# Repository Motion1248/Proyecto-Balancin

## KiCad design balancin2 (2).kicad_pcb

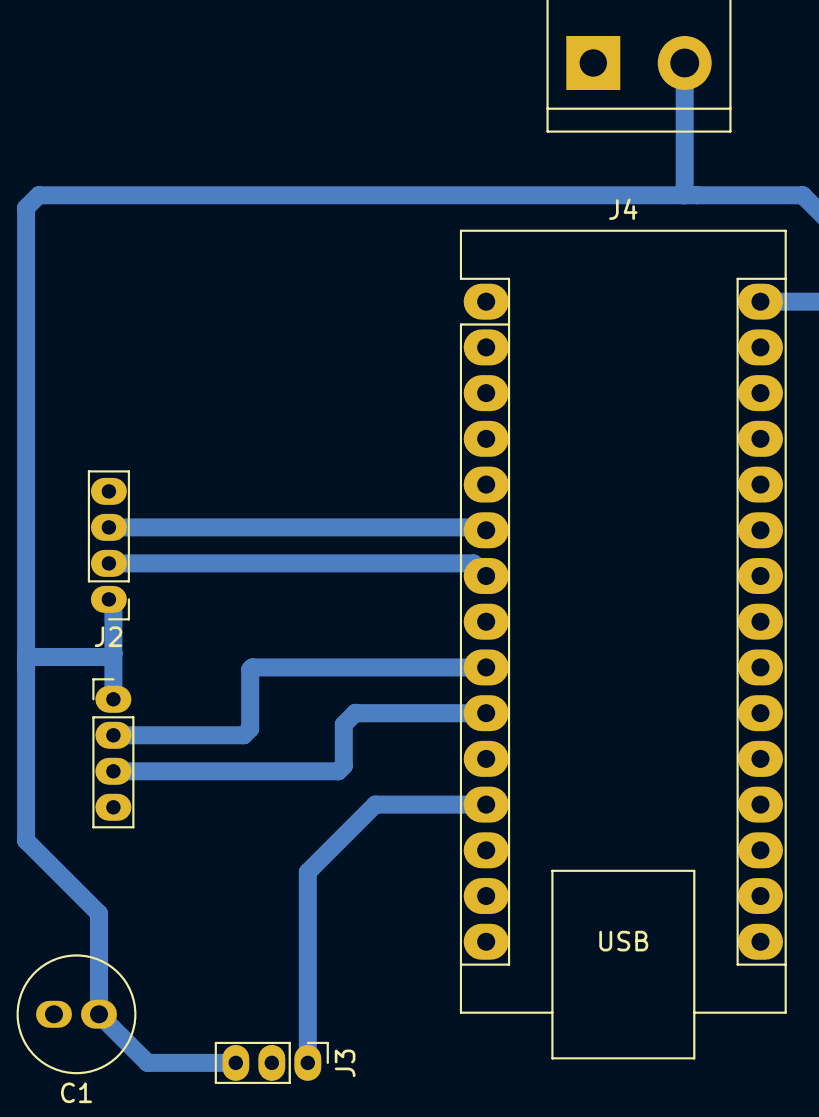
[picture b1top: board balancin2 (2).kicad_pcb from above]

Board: 2 copper layers, 6 parts (0 on the bottom side), 7 nets.

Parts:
C1: C; C_Radial_D6.3mm_H5.0mm_P2.50mm
J1, J2: Conn_01x04; PinHeader_1x04_P2.00mm_Vertical
J3: Conn_01x03; PinHeader_1x03_P2.00mm_Vertical
J4: Arduino_Nano_Header; Arduino_Nano
J5: Screw_Terminal_01x02; TerminalBlock_bornier-2_P5.08mm

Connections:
GND: C1.2, J1.4, J2.4, J3.2, J4.29 (GND), J5.1
unnamed: C1.1, J1.1, J3.3, J4.30 (VIN), J5.2
unnamed: J1.2, J4.9 (D6/AIN0)
unnamed: J1.3, J4.10 (D7/AIN1)
unnamed: J2.2, J4.7 (D4/T0)
unnamed: J2.3, J4.6 (D3/INT1)
unnamed: J3.1, J4.12 (D9/0C1)

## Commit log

2025-12-11 Add files via upload
    Esquemático
2025-12-11 Add initial servo control and measurement code
2025-12-15 Balancin
2025-12-15 Code
2025-12-15 Schematic
2025-12-18 Kicad PCB
2025-12-18 Rename Codigo to Programación/Código
2025-12-18 Update and rename Esquematico to Kicad sch/Esquemático
2025-12-18 Update and rename Placa to Kicad pcb/Placa
